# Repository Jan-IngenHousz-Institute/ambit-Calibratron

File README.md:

# new_Calibratron

The Calibratron rewritten for the ambit cmd-35 three-tier AS7341 chain
(`ambit/plans/AMBIT_COMMAND35_SPECPAR.md`). Self-contained: it does not import
the repo-root `helpers.py`.

```
spec_cal.py          pure - cmd-35 codecs, tier math, the tier-3 affine gate
quality.py           pure - the LED origin gate and the ADPD baseline gate
helpers.py           transport - discovery, Ambit link, references, record
run_calibratron.py   the bench sequence
tests/               78 tests, no hardware needed
```

Nothing here imports the repo-root `helpers.py` or `calibration_quality.py`.

Run: `python run_calibratron.py`  ·  Test: `python -m pytest tests -q`

## What it calibrates on the PAR chain

**`par_slope` and `par_intercept`. Nothing else.**

| vector | source | this script |
|---|---|---|
| `spec_offset[10]` | ams workbook — device-independent | reads back, verifies |
| `spec_sens[10]` | miniPar LR1-B seed (plan §7b) | reads back, records |
| `par_weight[10]` | miniPar Li-250A fleet seed, constrained fit (plan §7c) | reads back, records |
| **`par_slope`** | **per-device intensity sweep** | **fits, writes, verifies** |
| **`par_intercept`** | **same sweep** | **fits, writes, verifies** |

The three seeded vectors ship as firmware defaults. There is no code path here
that writes them, deliberately rather than by omission: a per-device tier-2 fit
from a single-lamp sweep scores R² −31 … −7443 with 434–779 % median error
(plan §2). An intensity sweep moves the sample along one ray in 10-space, so it
identifies a scale, not ten weights.

## What was dropped from the old Calibratron

| dropped | why |
|---|---|
| cmd 31 / `get_par` / `PAR` — the whole legacy PAR path | Integer `Spec_COE` weights on un-normalised counts at a pinned exposure, packed into a uint16 that wraps above ~11 % of full scale. A bright reading came back looking dark. |
| `set_par_gain` / `set_spec` writes | `spec_coef` is frozen (plan decision 7). Still **read** and recorded — cmd 31 and deployed devices depend on it — never written. |
| `ambit_spec_unscale`, `ambit_par_minipar_method`, `AMBIT_PAR_DISCREPANCIES` | All three existed to measure the gap between the legacy weighting and the MiniPAR's. Ambit now *ships* miniPar's fleet vector, so the gap they characterised is gone. |
| `basic_count_divisor` (seconds tick) | Replaced by `spec_cal.integration_time_ms`. The two differ by 1000×; keeping both invites picking the wrong one. |
| Origin-forced gating of the PAR fit | See below. |
| the repo-root `calibration_quality.py` | Replaced by `quality.py`, which fixes four things that were wrong for this bench — see below. The root module stays for the legacy script. |

Kept unchanged in substance: firmware flashing via `firmware_fetch`, device
naming, actinic-LED gain, ADPD dark baseline, openJII publish.

## The ADPD photodiodes during both sweeps

`RECORD_ADPD_TRACES = True` records an `arrun2` trace — **leaf, sun**, s_630,
r_630, env — at every point of *both* sweeps, and prints a per-point table.
Nothing is fitted or written from these; they go in the record for later
analysis.

The tier-3 sweep is the valuable one: it pairs the photodiodes with a
**calibrated PAR reference across the whole lamp range**, which is a PAR response
curve for `leaf` and `sun` obtained for free, at `actinic = 0` so they see the
same light the reference does. The LED sweep records them at `actinic = setting`,
where the Ambit's own LED is the source.

Three things the implementation has to get right:

- **The ADPD pulse LEDs are zeroed before every trace.** Without
  `set_currents,0,0,0` the detector sees its own 620/720/IR pulses and `sun` /
  `leaf` stop being a measurement of the incident light. Re-asserted per trace
  rather than once per sweep: it costs one write, and if anything reset the device
  mid-sweep the currents would come back non-zero and every later reading would be
  contaminated with nothing in the record saying so.
- **The trace comes last at each point.** It zeroes the pulse LEDs and drives the
  actinic, both of which change what the AS7341 sees, so it must not precede the
  cmd-35 read it is paired with.
- **Saturation is detected per channel.** A pinned photodiode is the failure that
  quietly ruins a later analysis — the samples stay plausible and the spread
  collapses to zero. `summarize_arrun` flags any channel within 1 % of the 24-bit
  ceiling, the table marks it `!`, and `assess_adpd_sweep` names the drive it
  pinned at. It also reports a dead or reversed channel. All **reported, never a
  gate**: a flat photodiode must not discard an otherwise good tier-3 fit.

Cost is about 0.5 s of trace plus overhead per point, ~14 s across both sweeps.
Cheaper than the old script's version, which opened and closed the port per point
and so paid a device reset and boot each time. `s_730` / `r_730` stay empty
because the run is type 2 (no IR reflect); `sun` and `leaf` are populated only
because ambient sub-sampling is 1.

## Why the PAR fit needs its own quality gate

`calibration_quality.assess_origin_fit` fits `y = k·x` and uses a free-intercept
fit as a *failure detector* — an intercept above 5 % of full scale means the
origin model was wrong, so it rejects. Tier 3's intercept is a **deliverable**,
so that logic inverts: the thing being measured becomes grounds for rejection.

The deeper cost is what origin-forcing does to the numbers. With a true
`b = 7.983` — the value plan §7c measured on the superseded OLS seed, 2.40 µmol
of dark-offset term plus 5.61 µmol of miniPar's discarded tier-2 intercept —
forcing through the origin folds the offset into the slope. At the bright end that is a sub-1 % error; at
120 tier-2 counts it is over 5 %, and it keeps growing as the light drops. **A
constant additive error becomes a proportional one, worst exactly where canopy
and shade measurements live.** `tests/test_spec_cal.py::test_origin_forcing_would_misplace_a_real_intercept`
pins that.

Two further incompatibilities: R² scored against the origin-forced prediction
gates on "did `b` happen to be small" rather than on linearity; and the
non-negativity check rejects a legitimately slightly-negative `par_tier2` at the
dark point, which the seeded `par_weight` (negative on NIR) can
produce. That is the one point the intercept is fitted from.

So `spec_cal.assess_affine_fit` fits both parameters, bounds-checks them against
the firmware predicates (`par_slope` ∈ (0,100], |`par_intercept`| ≤ 500), scores
R²/NRMSE against the affine prediction, permits negative inputs, and demotes the
intercept-size question to a *note* keyed on the dimmest lit point rather than a
rejection.

## What `quality.py` fixes in the root `calibration_quality.py`

The root module's arithmetic is fine and the legacy script still uses it. Four
things were wrong for the new approach, and `quality.py` is a straight
replacement rather than a wrapper because two of them are API shape:

1. **Its low coefficient bound was inclusive where the firmware's is exclusive.**
   `valid_actinic_coefficient` is `> 0.01 && <= 1.0`, and ambit's own test
   asserts *"actinic lower bound is exclusive"*. The host gate was
   `coefficient_min <= coefficient`, so a fit of exactly `0.01` **passed host QC
   and was then refused by the device** — the bench would report a successful
   write with nothing changed. Same class as sending an unrounded `par_slope`.
2. **One gate was dead at the only call site.** The old signature was
   `(x, y, stimulus)` and `calibrate_led` passed the LED settings as *both* `y`
   and `stimulus`, so *"reference readings are not monotonic with the applied
   stimulus"* compared the settings to themselves and could never fire.
   `assess_led_fit(measured, settings)` takes two arguments, which makes the
   mistake impossible instead of merely unlikely.
3. **A slightly negative dark reading failed the whole sweep closed.** Any
   negative value tripped *"calibration values must be non-negative"*. The
   MiniPAR reports `par_raw * slope + intercept`; with a negative intercept a
   genuinely dark reading comes back a shade under zero. That is noise. Small
   negatives are now clamped with a note; large ones still fail.
4. **Its thresholds shared names with different values in `spec_cal`.** Both
   defined `MIN_R2`, `MAX_NRMSE` and `MAX_MONOTONIC_REVERSAL`, at 0.99/0.05/0.02
   against 0.995/0.03/0.02. Two places to get a tuning edit wrong. Every
   threshold here is prefixed `LED_*` or `ADPD_*`, and a test asserts the names
   cannot collide.

The ADPD baseline gate moved out of the runner into the same file, so every
numerical gate the bench applies now sits next to the firmware bound it mirrors.

The origin fit itself is **kept, and is correct here**: zero drive is zero light
with no offset to absorb, so a free intercept is evidence against the model
rather than a quantity to fit — the opposite of tier 3.

One honest caveat on what the LED step buys you: as of `ambit@fix/spec_overflow`,
`actinic_coef` is validated, persisted and printed but **never applied** —
`AS_LED_Current()` takes the requested setting directly. So the step
characterises the LED rather than changing device behaviour. Worth running, worth
not over-trusting. Noted in the function's docstring too.

## The MiniPAR as reference instead of a Li-250A

Accepted. The cost is smaller than it looks, for a structural reason.

Ambit's seeded `par_weight` **is** miniPar's fleet vector, so at any single
calibration spectrum both instruments compute `w · s` over the same weights.
Whatever spectral bias `w` carries at that spectrum is common-mode and divides
out of the ratio, leaving the fitted slope as (near enough) the pure
optical-throughput ratio of the two stacks. The MiniPAR behaves as a **transfer
standard**, and the fit's *linearity* is untouched — which is why the QC gates
still mean what they say.

What it costs is a pure multiplicative bias: the reference MiniPAR's own PAR
error at the calibration lamp's spectrum.

| term | figure | source |
|---|---|---|
| MiniPAR in-domain | 1.96 % median, R² 0.9983 | plan §7c, 462 samples, 3.7–2033.7 µmol |
| MiniPAR cross-source | **4.37 % median, 9.82 % worst device** | plan §2, LED-calibrated → scored on daylight |
| Li-250A absolute accuracy | ~5 % | Li-Cor spec, unavoidable either way |
| **combined** | **~7 % typical, ~10 % worst** | in quadrature |

The cross-source row is the honest one: the bench lamp is halogen, which is not
in miniPar's daylight-dominated calibration set. So the choice takes you from
~5 % to ~7 %.

**It is recoverable without redoing bench work.** The record stores `par_tier2`
per sweep point, so one later Li-250A comparison on a single device yields a
scale correction applicable to every stored sweep. That is why the payload
carries the whole sweep and not just the fitted pair.

Two caveats the record captures rather than hides:

- **The sweep is not one spectrum.** A halogen lamp from 0.4 A to 6.6 A shifts
  colour temperature by hundreds of kelvin. Both instruments see it and use the
  same weights, so it largely cancels — but `spec_cal.spectral_drift` measures how
  far it moved, because that bounds how far the fitted slope travels from this
  lamp.
- **`par_slope` far from 1.0 is informative.** `par_tier2` is already in µmol
  (plan §7c fitted `w` to produce them directly, and a tier-3 refit on miniPar
  data returns `a = 1.0000`). A slope outside 0.2–5.0 means ambit's optics differ
  from miniPar's by more than that, or the reference is misconfigured. Noted, not
  rejected — nobody has measured ambit optics yet.

## A clipped point cannot be fitted — including the dark one

Found while checking the plan against the sweep design; now written into plan §7c.

Plan §7c justifies reusing miniPar's `par_weight` at all by showing that ambit's
extra offset subtraction costs a *constant* `Σ wᵢ·offsetᵢ` — 1.09 µmol on the
current seed, 2.40 on the superseded OLS one — which tier 3's intercept absorbs
exactly. **That constancy holds only while no channel
is clipped.** Once `s` saturates at zero the offset term stops being constant and
the relation stops being affine — and the clip is the chain's only nonlinearity
(§5).

This became live rather than theoretical when the real ams offsets replaced
zeros: with a zero offset vector `s == x` always and nothing can ever clip. The
offsets are only **0.28 – 2.02 raw counts** at the pinned 2× / 139 ms, so the
clip bites solely in a light-tight fixture — but there it bites on all ten
channels at once, which is exactly the dark point of a sweep.

Concretely: a fully clipped dark reading has `par_tier2` identically 0 against a
reference of ~0, so it lies on the line only if `par_intercept` is 0. Folding it
into the fit drags the intercept from 7.983 to 4.78 — **40 % low — while R² stays
above 0.99, so no quality gate catches it.**
(`tests/…::test_fitting_a_clipped_dark_point_would_bias_the_intercept`.)

So `spec_cal.usable_for_fit` rejects any clipped point at any lamp drive, and the
sweep gained a 0.4 A step: 0.0 A stays as the cheapest light-tightness check, and
0.4 A is a genuine low anchor inside the linear regime. If the dark point comes
back unclipped it is fitted too — the rule keys on `clip_mask`, not on the drive.

## The `par_weight` seed has a generation, and it changed

`SEED_PAR_WEIGHT` is the **constrained** miniPar fleet fit — `lsq_linear` on
basic counts with `F1–F8 ≥ 0` and Clear/NIR free, shrunk toward `W_TARGET` at
λ=0.03, exported by `miniPar/new_calibration_miniPAR/par_coeffs_fleet.json`.
`SEED_GENERATION` is `minipar-2026-08-18-constrained`.

It replaced a plain OLS fit on the same 462 samples. That one predicted in-domain
PAR just as well (in-sample R² 0.9984 against 0.9982) but its signs were not
physical — negative on F3, F5 and F8, positive on Clear — because the design
matrix has condition number ≈ 451 on a daylight-dominated set. The practical cost
is leverage on spectral shape rather than in-domain error: L1 norm 1172 against
457 for a 1.8× larger net response, and off-daylight it shows up directly —
canopy PAR spread 6.2 % against 0.4 %, coefficient direction spread p95 62° against 8°.

Two things follow for this script:

- **A tier-3 fit is only interpretable against the tier-2 vector it sat on.** The
  two vectors give tier-2 values within 5–8 % of each other on the bench lamp, so
  a re-swept `par_slope` moves by about that much and no gate would notice. Every
  record therefore carries `seed_generation` *and* `par_weight_generation`.
- **A device on older firmware must be named, not called unknown.** A `False` in
  `seed_match` means "someone wrote a fitted vector here" everywhere else, so
  `SUPERSEDED_PAR_WEIGHTS` keeps the previous vector and
  `SpecCal.par_weight_generation()` reports `minipar-2026-08-17-ols` for it.
  `read_par_provisional` adds a reason saying to reflash before trusting a fit
  taken on it.

`spec_sens` and `spec_offset` were already bit-for-bit the current
`spectral_coeffs_fleet.json` export and did not change. `bit8` stays clear: this
is still a fit on miniPar optics, not an ambit one. And the export still carries
`prior_is_placeholder: true`, so expect one more generation once the CM weights
are computed.

## How this host reads the flags word

The firmware zones `flags` into two bytes of **opposite polarity**, and it is
worth understanding before writing any host code against it:

| | | |
|---|---|---|
| low byte | conditions, `1` = needs attention | bit0 full scale · bit1 dark-offset clip · bit2 ASAT · bit3 acquisition fault |
| high byte | calibration, `1` = **confirmed** | bit8 `par_weight` is an ambit fleet fit · bit9 tier 3 stored for this device |

An all-zero word — what a truncated or zeroed frame produces — therefore reads
as "no fault reported, nothing confirmed calibrated", which is the pessimistic
reading. Confirmation requires bits to be **set**; treating an unset bit as
trustworthy is the failure the zoning prevents. So `par_provisional` here is
`not (bit8 and bit9)`, and `spec_cal.py` never collapses the two.

Two consequences for this script:

- **bit8 stays clear after a successful calibration**, because
  `AMBIT_PAR_WEIGHT_IS_AMBIT_FIT` is compile-time `false` until the ambit
  Li-250A campaign lands. Every device the Calibratron produces will report
  provisional PAR. That is correct, and it is never a success criterion here —
  the criteria are the cmd 33/4 read-back and the confirmation pass.
- **bit9 is authoritative for "has this device been swept"**, keyed on NVS key
  presence. `read_par_provisional` still cross-checks it against the read-back
  vectors, but the check is **directional**: bit9 latches for the life of the
  NVS partition (there is no verb to delete the key — firmware plan §5a), so
  bit9 set over identity vectors is a legal state (a bench write, or a slope
  restored to exactly 1.0) that earns a printed reason and nothing more. Only
  the impossible direction — bit9 clear over non-identity vectors — **aborts
  the sweep**, because a fit taken on top of an unknown tier-2 state is not a
  calibration.

**The reboot dump does not contain the PAR chain.** The five vectors live outside
`ambit_calibration_info_t` by design (decision 2), so the boot banner shows a
device that looks fully calibrated while its PAR chain is untouched. Every step
here reads cmd 33/4 alongside the dump, and read-back verification goes through
cmd 33/4, never through `ambit_reboot`.

**Writes have three outcomes, not two.** `report_spec_save` answers
`"<what> saved and verified"`, `"<what> rejected"`, or
`"<what> save failed: <ESP_ERR_…>"`. The third contains no negative keyword, so a
host testing for `"rejected"` reads an NVS failure as a success. Acceptance is
tested **positively** on `saved and verified` — one test that covers all three
outcomes and any future rewording.

**`get_spec_cal` is five labelled lines**, not one CSV row:
`spec_offset:` / `spec_sens:` / `par_weight:` (ten `%.9g` each) then `par_slope:`
and `par_intercept:`. `parse_spec_cal_text` keys on the labels, never on
position — a one-slot shift in these vectors is undetectable in the numbers,
since every element is a plausible magnitude for its neighbour. `%.9g`
round-trips an IEEE-754 float exactly, so the text mirror and cmd 33/4 agree bit
for bit.

## Bench sequence

```
probe cmd 35 (80 B, format 1)          -> abort tier 3 if absent; no legacy fallback
read cmd 33/4                          -> previous tier 3, for rollback
verify firmware math from raw[]        -> catches tick / gain ordinal / bank / NIR-Clear
sweep 0.0 .. 6.6 A                     -> par_tier2 vs reference PAR, per-point masks
affine fit + QC
write par_slope, par_icept             -> verify via cmd 33/4, roll back on mismatch
confirm at 0.8 / 3.0 / 6.6 A           -> device par vs reference, closed loop
```

The firmware-math check is the one that earns cmd 35's design: `raw[]` stays on
the wire so the host can reproduce every derived field, and a single comparison
covers all four footguns in plan §8 — each of which is otherwise invisible at the
pinned exposure. If it fails, the run stops before the fit, because a fit taken
on wrong arithmetic would encode the bug as a calibration coefficient.

## Every MiniPAR read is a coin flip unless the port is opened cold

The MiniPARs are ESP32-class boards with reset wired to DTR/RTS, so pyserial's
default open — which asserts both — reboots the instrument. The command then goes
into a booting device and the reply is one of:

```
Saved PC:0x40053b60          bootloader output
load:0x3fcd5810,len:0x438    bootloader output
error:unknown_command        the command line, chewed up by the reset
17.056                       the previous question's answer, still buffered
```

Only the last one is dangerous: it parses. A stale `par` reading pairs the wrong
reference with the Ambit's `par_tier2`, and the fit absorbs it silently.

So `helpers._query` opens cold (`open_serial_no_reset`, DTR/RTS set *before*
open), drops whatever is already buffered, skips bootloader lines without
spending an attempt, and re-asks up to `QUERY_ATTEMPTS` times whenever the reply
is an `error:` or the wrong *shape* for the question — every getter passes what
shape it expects. `_command` is deliberately left on the default open: its only
user is the Kiprim DC source, which has no reset on those pins and may hold its
output until DTR is asserted.

A reference that still will not answer raises `ReferenceUnavailable` rather than
returning a number: the tier-3 sweep aborts with `status:
reference_unavailable`, writes nothing, and drops the lamp to 0 A in a `finally`.
A partial sweep against a silent reference is not a calibration.

## BAD COMMAND: one space in a command template

`set_currents` is implemented in every firmware this bench flashes
(`ambit/src/do_command.h`, `case hash("set_currents")`, printing `Currents set to
%d, %d, %d`). Six `BAD COMMAND` replies to it per run were not a missing verb.
They came from the **trailing space** in `arrun1` / `arrun2`'s padding, `",
, 
"`.

The device reads each command with `Serial_Input_Chars(choose, ":,", 200, ...)`, and
`serial.cpp` gives that reader three relevant properties:

- `:` and `,` end a token and are discarded;
- CR/LF are skipped **without being stored** and without restarting the timer;
- anything else is stored, and storing restarts a **200 ms** inter-character window.

A space is printable, so it is stored as token byte 0 and opens that window.
Whatever the host sends inside it joins the same token, so `set_currents,0,0,0,`
arrives as `" set_currents"` - and `do_command()` drops any token whose first
character fails `isalnum()`, silently. The verb is gone. Its three `0` arguments
are then read as commands, and a digit-leading token goes through `atoi` into a
switch with no numeric cases: `BAD COMMAND`, three times.

Why the first trace of each sweep always worked: `set_actinic` sleeps 0.3 s and
flushes, which outlasts the 200 ms window. `arrun` returned the instant it saw
`Data sent` and did not - so traces 2..7 lost their `set_currents` and the ADPD
pulse LEDs stayed live through the rest of the sweep.

Fixed at the root (padding is now `",
,
"`, which stores nothing) and defended
at the host (`AmbitLink._settle_console`, `CONSOLE_TOKEN_SETTLE_S = 0.25`, after
every trace). `AmbitLink.text` also takes `expect=` now, which was a real fix for
stale-line attribution but was NOT this bug - there was no acknowledgement to
find, because the verb never reached the parser.

`tests/test_console_tokenizer.py` models the reader's three rules and asserts the
next verb survives each padded template; it also asserts the old padding fails,
so the guard is shown to catch what it was written for.

The consequence was not cosmetic: `pulse_currents_zeroed` was `False`, so `leaf`
and `sun` in those traces measured the Ambit's own pulse LEDs alongside the
incident light. That flag now travels beside `adpd_stats` (raw samples are
dropped, provenance is not), the station block reports
`pulse_leds_zeroed_confirmed` rather than asserting the intent, and one line under
the table tells the operator the numbers are contaminated.

## `leaf` and `sun` face different directions

Which photodiode responds is fixture geometry, not detector health:

| sweep | `leaf` | `sun` |
|---|---|---|
| halogen lamp, 0.0-6.6 A | span 69, wanders | **span 927, monotonic** |
| Ambit actinic LED, 10-250 | **790 -> 1134, monotonic** | flat at ~655 |

So `assess_adpd_sweep` takes `responders=` and only the channel aimed at the
source gets the flat / non-monotonic notes - `("sun",)` for the lamp sweep,
`("leaf",)` for the LED sweep. The other channel is still recorded, and
saturation is still reported for both: a pinned photodiode is a fault wherever it
points. Before this, every run reported the geometry as a fault, which is how a
genuinely flat channel would have gone unnoticed.

`env` is not a photodiode at all - it is the MLX object temperature, sampled once
per trace rather than once per pulse. Its `+-0.0` is arithmetic on a single value,
not an unusually quiet channel, and the object cannot warm measurably inside a
0.5 s trace.

## A missing instrument stops the bench

`REQUIRE_ALL_DEVICES` (default on). A role that does not answer used to degrade
quietly: tier 3 printed one `[skip]` line and the run still saved and uploaded a
record. Discovery failing is a bench fault, so it now aborts before the reboot
dump and before the rename prompt - nothing has been touched at that point.

Discovery also says *why* now. A port that is present but will not open used to
be a `logger.debug` line, which made it indistinguishable from an unplugged
instrument; both are warnings, and the "no device for role" message lists every
port that was actually asked.

## Status

The firmware side this host talks to is **built**, on `ambit@fix/spec_overflow`:
the cmd-35 payload, cmd 33/4, the five text setters, `get_spec_cal`, the
predicates, the two-zone flags word, and the seeded `spec_sens` / `par_weight`
in `nvs1.h` are all in place. Verified against the source, not assumed.

What is still open is measurement, not code (plan §11): no vector here is fitted
on ambit hardware. `AMBIT_PAR_WEIGHT_IS_AMBIT_FIT` is `false`, so bit8 stays
clear and every device this bench produces reports provisional PAR — as it
should, until an ambit Li-250A campaign replaces §7c.

## Desktop GUI

`calibratron_gui.py` is a tkinter front-end over `run_calibratron.py`: the same
per-device pass (flash, name, tier-3 PAR, actinic LED, record, publish), with
the bench instruments confirmed from the cached port roles for every device and
the openJII sign-in kept for the whole session.

Download the ZIP for your platform from this repository's GitHub Releases:

- `calibratron-windows-x64.zip`: extract the whole folder and run `calibratron.exe`.
- `calibratron-linux-x64.zip`: extract and run `calibratron/calibratron` (Ubuntu 22.04 or newer).
- `calibratron-macos-arm64.zip`: extract and open `calibratron.app` (Apple Silicon).

Keep the bundle's supporting files beside the executable. Python and esptool do
not need to be installed separately; the serial drivers and the bench hardware
are still required. The bundles are unsigned, so Windows and macOS may show an
unknown-publisher warning. Intel macOS is not packaged.

For a source checkout, install `requirements-gui.txt` (Linux also needs the
distribution's `python3-tk`), then run `python calibratron_gui.py`. Press
**Rescan bench**, select the steps, and press **Start calibration**.

Packaged applications keep `calibrations/`, `firmware_cache/` and the
`.port_roles.json` port hints beneath a per-user data directory
(`runtime_paths.data_dir()`):

| Platform | Data directory |
| --- | --- |
| Windows | `%LOCALAPPDATA%/Calibratron` |
| macOS | `~/Library/Application Support/Calibratron` |
| Linux | `${XDG_DATA_HOME:-~/.local/share}/Calibratron` |

Set `CALIBRATRON_DATA_DIR` to override it. A source checkout uses the checkout
folder itself. The firmware release is resolved once per session: the first
device asks GitHub, every later device reuses that answer. The downloaded
firmware cache is kept when the GUI closes, so the next session re-proves the
release online and falls back to the cached copy if GitHub will not answer
(anonymous API calls are limited to 60 per hour per public IP). API-key
settings live in the separate per-user configuration directory managed by
`openjii_auth.py`.

## GUI release pipeline

`.github/workflows/gui-release.yml` tests and builds Windows x64, Linux x64 and
macOS ARM64 bundles on pull requests, pushes to `main`, and manual runs. Every
platform runs the packaged executable's `--smoke-test`, which constructs the
GUI without signing in, loads the bundled CA roots, and exercises the bundled
esptool without touching a serial port. PR and manual runs leave the ZIPs as
Actions artifacts.

After all three builds pass on `main`, the same run's ZIPs and `SHA256SUMS` are
uploaded to a draft release and then published. Tags are `calibratron-vX.Y.Z`
and the patch number increments automatically; re-running an already published
commit does not create another release. Publication uses the built-in
`GITHUB_TOKEN`: no extra secret and no hand-made tag. The workflow builds the
merged `main` commit, so merge commits, squash merges and direct pushes all
release the same way.

Local rehearsal of what CI does:

```bash
python -m pip install -r requirements-build.txt
python -m pytest tests -q
pyinstaller --noconfirm --clean --onedir --windowed --name calibratron \
  --paths . --collect-all esptool packaging/launcher.py
dist/calibratron/calibratron --smoke-test     # Linux: xvfb-run -a ...
```

Automated packaging checks do not replace a physical bench test.

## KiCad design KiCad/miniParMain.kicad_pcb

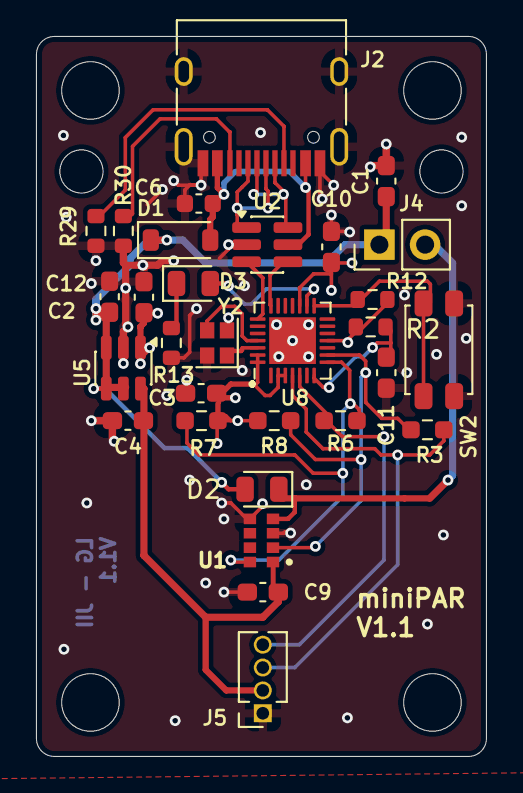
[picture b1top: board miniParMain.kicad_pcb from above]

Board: 4 copper layers, 25.0 x 40.0 mm, 30 parts (0 on the bottom side), 22 nets.

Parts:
C1, C2, C3, C4, C9, C10, C11, C12: 2.2u; C_0603_1608Metric_Pad1.08x0.95mm_HandSolder
C6: 10u; C_0603_1608Metric
D1: 1N4148WT; D_SOD-123
D2, D3: LED; D_0805_2012Metric
J2: USB_C_Receptacle; USB_C_Receptacle_HRO_TYPE-C-31-M-12
J4: Conn_01x02_Pin; PinHeader_1x02_P2.54mm_Vertical
J5: secondBoard; PinSocket_1x04_P1.27mm_Vertical
R2, R12, R13, R29, R30: 5.1K; R_0603_1608Metric
R3, R6: 0R; R_0603_1608Metric_Pad0.98x0.95mm_HandSolder
R7, R8: 10K; R_0603_1608Metric_Pad0.98x0.95mm_HandSolder
SW2: SW_Push; SW_SPST_EVQP2_ShortPushTravel_H2.1mm
U1: AS7341-DLGT; PSON80P310X200X110-8N
U2: IP4234CZ6; SC-74-6_1.55x2.9mm_P0.95mm
U5: AP7312-1833W6-7; TSOT-23-6
U8: ESP8685; QFN-28-1EP_4x4mm_P0.4mm_EP2.6x2.6mm
Y2: 40MHz; Crystal_SMD_2016-4Pin_2.0x1.6mm

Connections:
BOOT: R12.1, SW2.1, U8.15 (GPIO9/BOOT)
CC1: J2.A5 (CC1), R29.2
CC2: J2.B5 (CC2), R30.2
D+: U2.3, U8.22 (GPIO19/USB_D+)
D-: U2.4, U8.21 (GPIO18/USB_D-)
GND: C1.2, C2.2, C3.2, C4.2, C6.1, C9.2, C10.2, C11.2, C12.2, J2.A1 (GND), J2.A12 (GND), J2.B1 (GND), J2.B12 (GND), J2.S1 (SHIELD), J5.1, R13.1, R29.1, R30.1, SW2.2, U1.3 (GND), U1.5 (PGND), U2.2 (VN), U5.2 (GND), U8.29 (GND), Y2.2, Y2.4
LED1ACT: D2.1 (K), J4.2, U1.4 (LDR)
unnamed: D3.2 (A), U8.16 (GPIO10)
unnamed: D3.1 (K), R13.2
unnamed: J2.A6 (D+), J2.B6 (D+), U2.1
unnamed: J2.A7 (D-), J2.B7 (D-), U2.6
unnamed: U8.25 (XTAL_N), Y2.3
unnamed: U8.26 (XTAL_P), Y2.1
SCL: R3.2, R8.1, U1.2 (SCL), U8.9 (MTMS/GPIO4/ADC1_CH4)
SCL_2: J5.4, R6.1, U8.5 (GPIO1/XTAL_32K_N/ADC1_CH1)
SDA: R6.2, R7.1, U1.8 (SDA), U8.8 (GPIO3/ADC1_CH3)
SDA_2: J5.3, R3.1, U8.4 (GPIO0/XTAL_32K_P/ADC1_CH0)
V+: C1.1, C12.1, D1.1 (K), D2.2 (A), J4.1, U5.3 (EN2), U5.4 (EN1), U5.5 (VIN)
V+1.8V: C4.1, C9.1, J5.2, U1.1 (VDD), U5.6 (VOUT_1V8)
V+3V: C2.1, C3.1, C10.1, R2.1, R7.2, R8.2, R12.2, U5.1 (VOUT_3V3), U8.2 (VDD3P3), U8.3 (VDD3P3), U8.11 (VDD3P3_RTC), U8.17 (VDD3P3_CPU), U8.27 (VDDA), U8.28 (VDDA)
Vusb: C6.2, D1.2 (A), J2.A4 (VBUS), J2.A9 (VBUS), J2.B4 (VBUS), J2.B9 (VBUS), U2.5 (VP)
reset_EN: C11.1, R2.2, U8.7 (CHIP_EN)

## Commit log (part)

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2026-04-08 before merging with LG
2026-04-08 add kicad files - V1.0
2026-04-09 PCB revision -> V 1.1
2026-04-09 add bare minimum casing - diffuser holder
2026-04-16 add direct PAR readout and option to scale and calibrate dec
2026-04-20 add sandbox scripts for the callibration - MiniPar and Ambyte
2026-04-23 tested on windozed machine
2026-04-28 added JSON parsing feature, bug MCU not supported by openJII
2026-05-08 rationalizing 1/4
2026-05-08 rationalizing 2/4
2026-05-08 rationalizing 3/4
2026-05-08 rationalizing 4/4
2026-05-11 v.0.0.1
2026-05-12 mqtt support
2026-05-12 mqtt support, cleaned gitignore
2026-05-18 pre naming
2026-05-19 helper updated
2026-05-19 Apply .gitignore / clean cached files
2026-05-19 auto-install requirements
2026-05-20 Added firmware ambyte
    Changed current settings
2026-05-20 add script for the manual test
2026-05-21 updated fw ambit to 005
2026-05-21 adjusted 0.0.5 FW requirement
2026-06-08 adjusted the helper.py to ensure detection also in JN. Added SingleMiniPARCalibration notebook for calibration with only miniPAR
2026-06-19 added values to the payload
